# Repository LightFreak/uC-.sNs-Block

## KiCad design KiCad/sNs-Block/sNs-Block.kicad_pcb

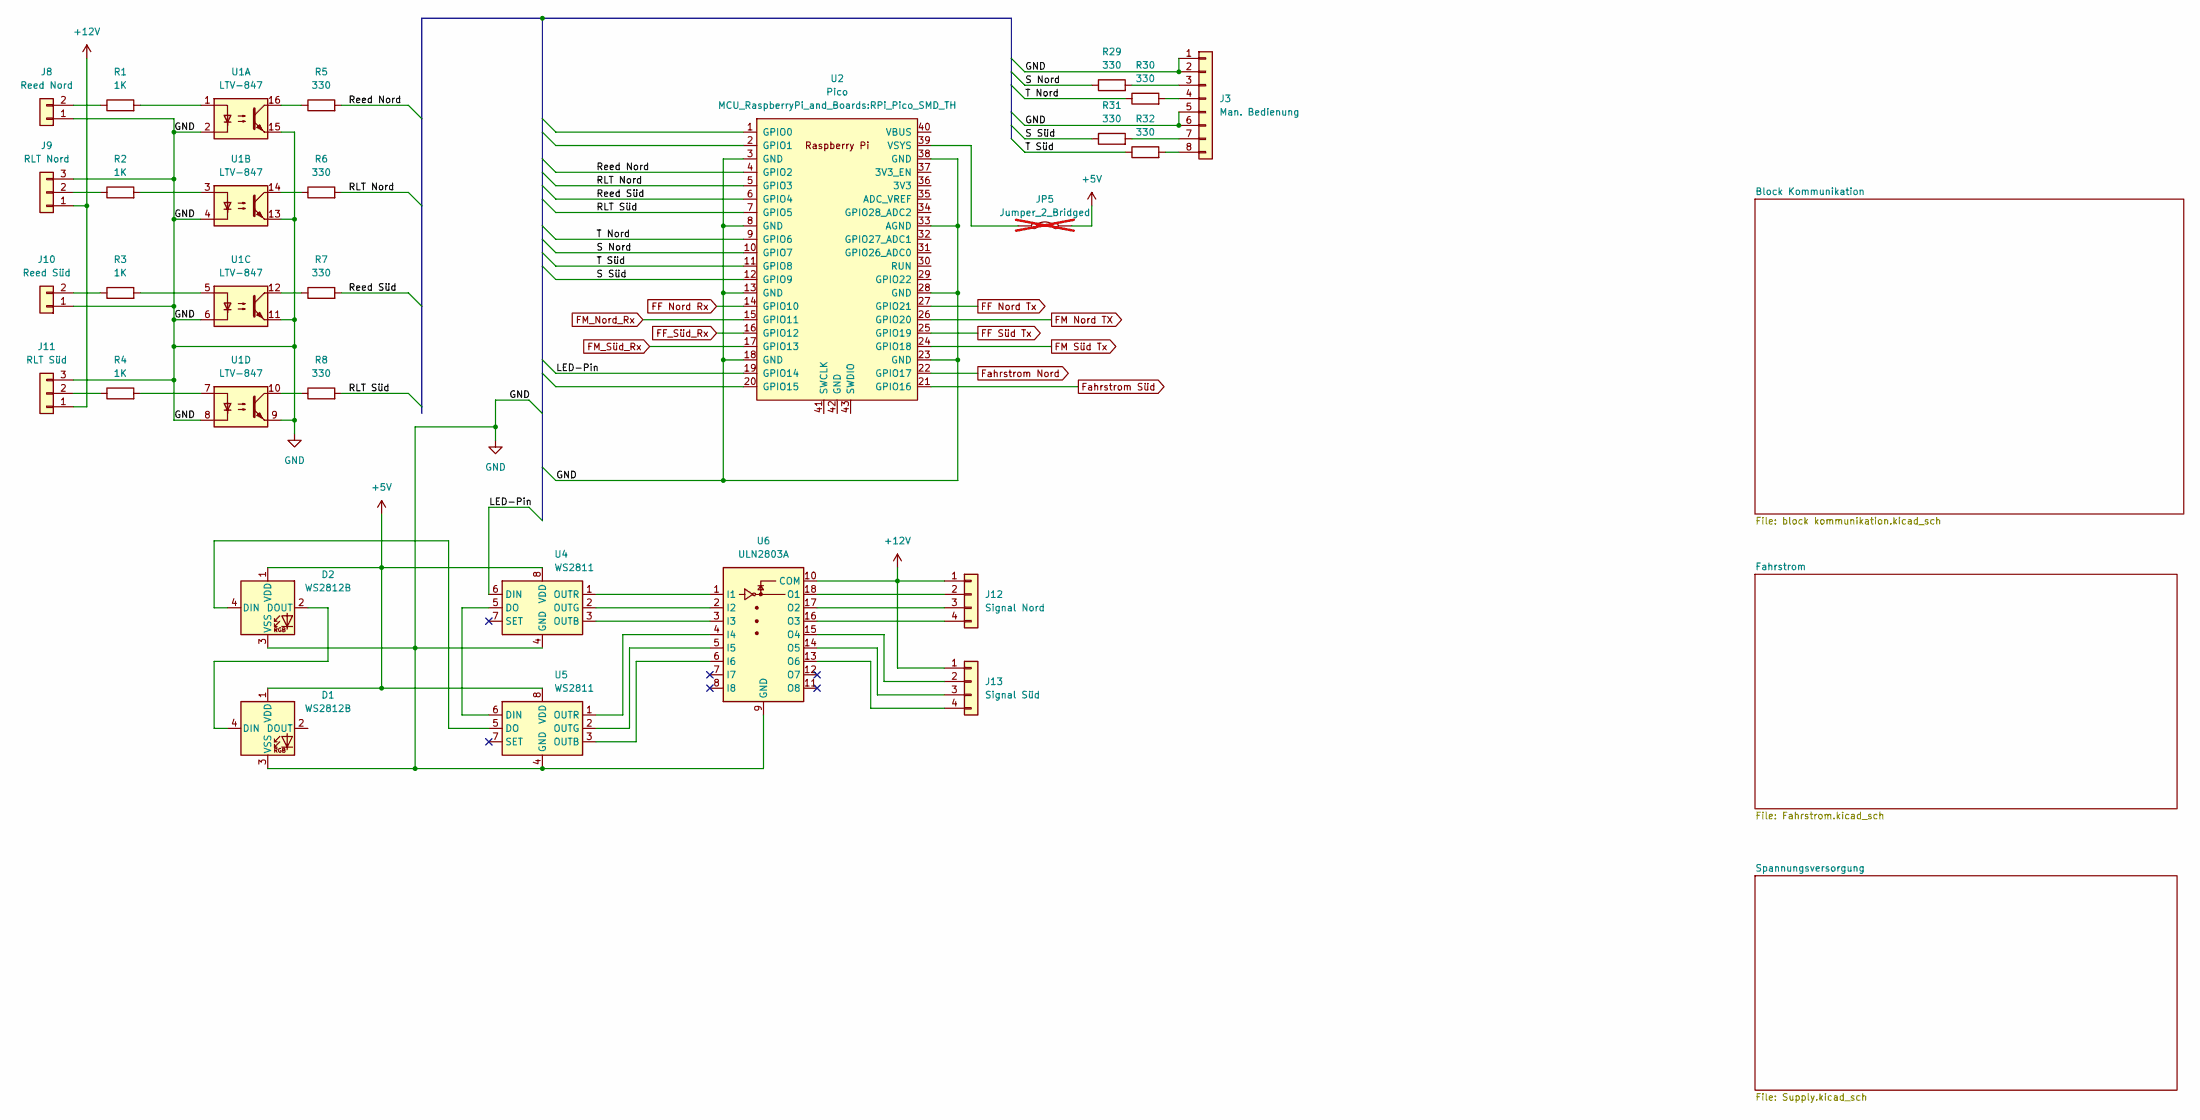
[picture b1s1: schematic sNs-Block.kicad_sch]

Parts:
D1, D2: WS2812B; LED_WS2812B_PLCC4_5.0x5.0mm_P3.2mm; Mouser 474-COM-24837
J3: Man. Bedienung; PinSocket_1x08_P2.54mm_Vertical; Mouser 571-3-641215-8
J8: Reed Nord; PinHeader_1x02_P2.54mm_Vertical; Mouser 571-6445182
J9: RLT Nord; PinHeader_1x03_P2.54mm_Vertical; Mouser 571-6404543
J10: Reed Süd; PinHeader_1x02_P2.54mm_Vertical; Mouser 571-6445182
J11: RLT Süd; PinHeader_1x03_P2.54mm_Vertical; Mouser 571-6404543
J12: Signal Nord; PinHeader_1x04_P2.54mm_Vertical; Mouser 571-6412154
J13: Signal Süd; PinHeader_1x04_P2.54mm_Vertical; Mouser 571-6412154
JP5: Jumper_2_Bridged; TestPoint_2Pads_Pitch5.08mm_Drill1.3mm; not fitted
R1, R2, R3, R4: 1K; R_0805_2012Metric_Pad1.20x1.40mm_HandSolder; Mouser 71-TNPW08051K00FEEA
R5, R6, R7, R8, R29, R30, R31, R32: 330; R_0805_2012Metric_Pad1.20x1.40mm_HandSolder; Mouser 71-CRCW0805330RJNEAH
U1: LTV-847; DIP-16_W7.62mm; Mouser 859-LTV-847
U2: Pico; RPi_Pico_SMD_TH; Mouser 909-RP2040-PICO
U4, U5: WS2811; DIP-8_W7.62mm; Mouser 485-1378
U6: ULN2803A; DIP-18_W7.62mm_Socket; Mouser 511-ULN2803A

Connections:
+5V: D1.1 (VDD), D2.1 (VDD), JP5.2 (B), U4.8 (VDD), U5.8 (VDD); also elsewhere on the board
+12V: J9.1, J11.1, J12.1, J13.1, U6.10 (COM); also elsewhere on the board
/LED-Pin: U2.19 (GPIO14), U4.6 (DIN)
/RLT Nord: R6.2, U2.5 (GPIO3)
/RLT Süd: R8.2, U2.7 (GPIO5)
/Reed Nord: R5.2, U2.4 (GPIO2)
/Reed Süd: R7.2, U2.6 (GPIO4)
/S Nord: R29.1, U2.10 (GPIO7)
/S Süd: R31.1, U2.12 (GPIO9)
/T Nord: R30.1, U2.9 (GPIO6)
/T Süd: R32.1, U2.11 (GPIO8)
FF Nord Rx: U2.14 (GPIO10); also elsewhere on the board
FF Nord Tx: U2.27 (GPIO21); also elsewhere on the board
FF Süd Tx: U2.25 (GPIO19); also elsewhere on the board
FF_Süd_Rx: U2.16 (GPIO12); also elsewhere on the board
FM Nord TX: U2.26 (GPIO20); also elsewhere on the board
FM Süd Tx: U2.24 (GPIO18); also elsewhere on the board
FM_Nord_Rx: U2.15 (GPIO11); also elsewhere on the board
FM_Süd_Rx: U2.17 (GPIO13); also elsewhere on the board
Fahrstrom Nord: U2.22 (GPIO17); also elsewhere on the board
Fahrstrom Süd: U2.21 (GPIO16); also elsewhere on the board
GND: D1.3 (VSS), D2.3 (VSS), J3.1, J3.2, J3.5, J3.6, J8.1, J9.3, J10.1, J11.3, U1.2, U1.4, U1.6, U1.8, U1.9, U1.11, U1.13, U1.15, U2.3 (GND), U2.8 (GND), U2.13 (GND), U2.18 (GND), U2.23 (GND), U2.28 (GND), U2.33 (AGND), U2.38 (GND), U4.4 (GND), U5.4 (GND), U6.9 (GND); also elsewhere on the board
unnamed: D1.4 (DIN), D2.2 (DOUT)
unnamed: D2.4 (DIN), U5.5 (DO)
unnamed: J3.3, R29.2
unnamed: J3.4, R30.2
unnamed: J3.7, R31.2
unnamed: J3.8, R32.2
unnamed: J8.2, R1.1
unnamed: J9.2, R2.1
unnamed: J10.2, R3.1
unnamed: J11.2, R4.1
unnamed: J12.2, U6.18 (O1)
unnamed: J12.3, U6.17 (O2)
unnamed: J12.4, U6.16 (O3)
unnamed: J13.2, U6.15 (O4)
unnamed: J13.3, U6.14 (O5)
unnamed: J13.4, U6.13 (O6)
unnamed: JP5.1 (A), U2.39 (VSYS)
unnamed: R1.2, U1.1
unnamed: R2.2, U1.3
unnamed: R3.2, U1.5
unnamed: R4.2, U1.7
unnamed: R5.1, U1.16
unnamed: R6.1, U1.14
unnamed: R7.1, U1.12
unnamed: R8.1, U1.10
unnamed: U4.5 (DO), U5.6 (DIN)
unnamed: U4.3 (OUTB), U6.3 (I3)
unnamed: U4.2 (OUTG), U6.2 (I2)
unnamed: U4.1 (OUTR), U6.1 (I1)
unnamed: U5.3 (OUTB), U6.6 (I6)
unnamed: U5.2 (OUTG), U6.5 (I5)
unnamed: U5.1 (OUTR), U6.4 (I4)

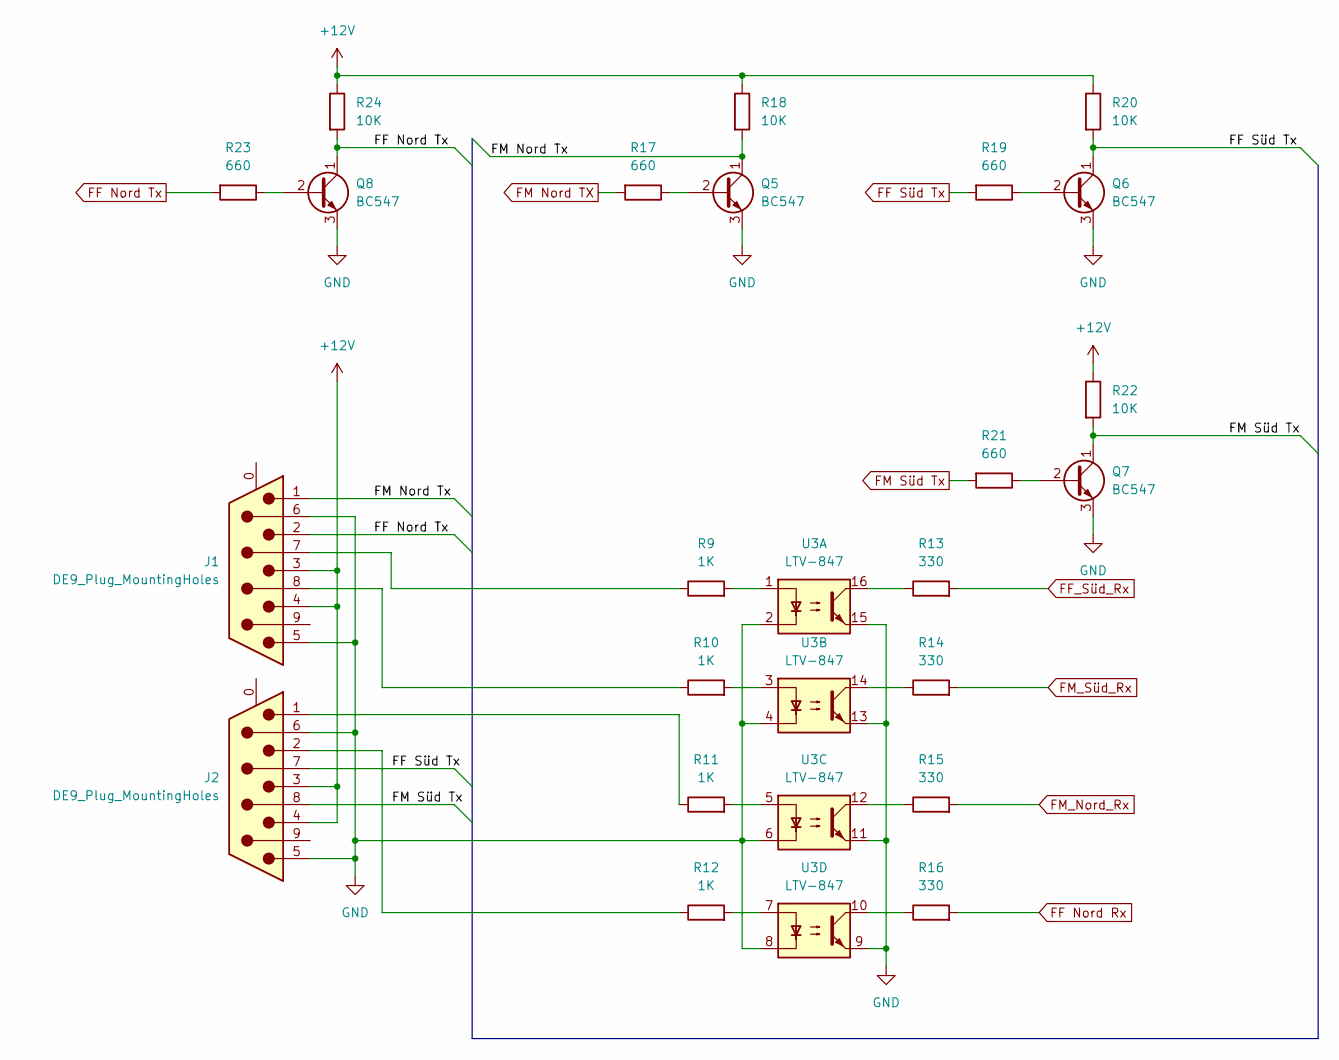
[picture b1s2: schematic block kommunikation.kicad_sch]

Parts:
J1: DE9_Plug_MountingHoles; DSUB-9_Female_Horizontal_P2.77x2.84mm_EdgePinOffset4.94mm_H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; Mouser 523-SDE09SA4CH3FC309
J2: DE9_Plug_MountingHoles; DSUB-9_Male_Horizontal_P2.77x2.84mm_EdgePinOffset4.94mm_Hou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; Mouser 706-163C17529X
Q5, Q6, Q7, Q8: BC547; TO-92_Inline; Mouser 637-BC547C
R9, R10, R11, R12: 1K; R_0805_2012Metric_Pad1.20x1.40mm_HandSolder; Mouser 71-TNPW08051K00FEEA
R13, R14, R15, R16: 330; R_0805_2012Metric_Pad1.20x1.40mm_HandSolder; Mouser 71-CRCW0805330RJNEAH
R17, R19, R21, R23: 660; R_0805_2012Metric_Pad1.20x1.40mm_HandSolder; Mouser 667-ERA-6AEB681V
R18, R20, R22, R24: 10K; R_0805_2012Metric_Pad1.20x1.40mm_HandSolder; Mouser 594-MCU08050D1002BP1
U3: LTV-847; DIP-16_W7.62mm; Mouser 859-LTV-847

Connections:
+12V: J1.3, J1.4, J2.3, J2.4, R18.1, R20.1, R22.1, R24.1; also elsewhere on the board
/Block Kommunikation/FM Nord Tx: J1.1, Q5.1 (C), R18.2
FF Nord Rx: R16.2; also elsewhere on the board
FF Nord Tx: J1.2, Q8.1 (C), R23.2, R24.2; also elsewhere on the board
FF Süd Tx: J2.7, Q6.1 (C), R19.2, R20.2; also elsewhere on the board
FF_Süd_Rx: R13.2; also elsewhere on the board
FM Nord TX: R17.2; also elsewhere on the board
FM Süd Tx: J2.8, Q7.1 (C), R21.2, R22.2; also elsewhere on the board
FM_Nord_Rx: R15.2; also elsewhere on the board
FM_Süd_Rx: R14.2; also elsewhere on the board
GND: J1.5, J1.6, J2.5, J2.6, Q5.3 (E), Q6.3 (E), Q7.3 (E), Q8.3 (E), U3.2, U3.4, U3.6, U3.8, U3.9, U3.11, U3.13, U3.15; also elsewhere on the board
unnamed: J1.7, R9.1
unnamed: J1.8, R10.1
unnamed: J2.1, R11.1
unnamed: J2.2, R12.1
unnamed: Q5.2 (B), R17.1
unnamed: Q6.2 (B), R19.1
unnamed: Q7.2 (B), R21.1
unnamed: Q8.2 (B), R23.1
unnamed: R9.2, U3.1
unnamed: R10.2, U3.3
unnamed: R11.2, U3.5
unnamed: R12.2, U3.7
unnamed: R13.1, U3.16
unnamed: R14.1, U3.14
unnamed: R15.1, U3.12
unnamed: R16.1, U3.10

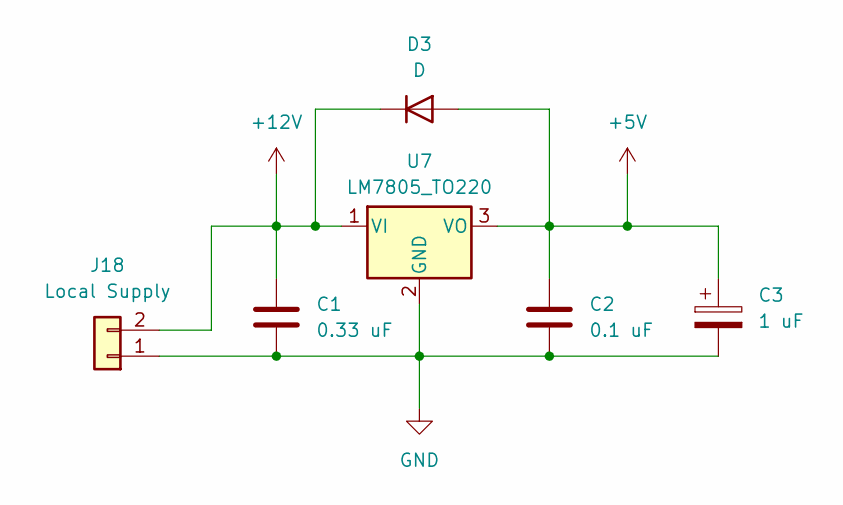
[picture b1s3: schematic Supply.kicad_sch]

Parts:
C1: 0.33 uF; C_0805_2012Metric; Mouser 667-ECH-U1H331JB5
C2: 0.1 uF; C_0805_2012Metric; Mouser 667-ECH-U1H101JX5
C3: 1 uF; CP_Radial_D10.0mm_P5.00mm; Mouser 871-B41821A6227M000
D3: D; D_DO-41_SOD81_P7.62mm_Horizontal; Mouser 637-1N4001
J18: Local Supply; PinSocket_1x02_P2.54mm_Vertical; Mouser 571-6445182
U7: LM7805_TO220; TO-220-3_Vertical; Mouser 926-LM7805CT/NOPB

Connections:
+5V: C2.1, C3.1, D3.2 (A), U7.3 (VO); also elsewhere on the board
+12V: C1.1, D3.1 (K), J18.2, U7.1 (VI); also elsewhere on the board
GND: C1.2, C2.2, C3.2, J18.1, U7.2 (GND); also elsewhere on the board

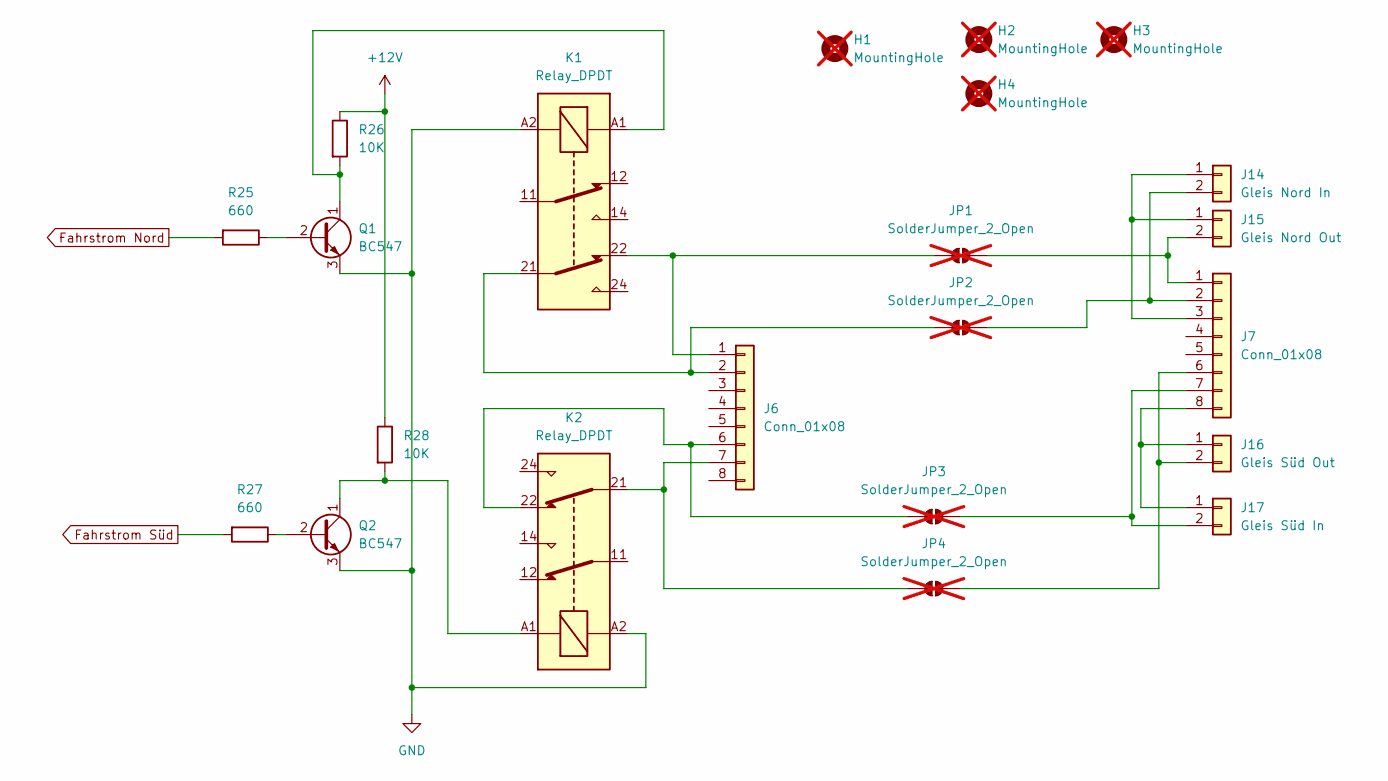
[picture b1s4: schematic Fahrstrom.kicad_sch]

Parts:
H1, H2, H3, H4: MountingHole; MountingHole_4.3mm_M4; not fitted
J6, J7: Conn_01x08; PinSocket_1x08_P2.54mm_Vertical; Mouser 571-3-641215-8
J14: Gleis Nord In; PinSocket_1x02_P2.54mm_Vertical; Mouser 571-6445182
J15: Gleis Nord Out; PinSocket_1x02_P2.54mm_Vertical; Mouser 571-6445182
J16: Gleis Süd Out; PinSocket_1x02_P2.54mm_Vertical; Mouser 571-6445182
J17: Gleis Süd In; PinSocket_1x02_P2.54mm_Vertical; Mouser 571-6445182
JP1, JP2, JP3, JP4: SolderJumper_2_Open; SolderJumper-2_P1.3mm_Open_TrianglePad1.0x1.5mm; not fitted
K1, K2: Relay_DPDT; Relay_DPDT_Finder_30.22; Mouser 653-G6A234PST15USD12
Q1, Q2: BC547; TO-92_Inline; Mouser 637-BC547C
R25, R27: 660; R_0805_2012Metric_Pad1.20x1.40mm_HandSolder; Mouser 667-ERA-6AEB681V
R26, R28: 10K; R_0805_2012Metric_Pad1.20x1.40mm_HandSolder; Mouser 594-MCU08050D1002BP1

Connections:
+12V: R26.1, R28.1; also elsewhere on the board
Fahrstrom Nord: R25.2; also elsewhere on the board
Fahrstrom Süd: R27.2; also elsewhere on the board
GND: K1.A2, K2.A2, Q1.3 (E), Q2.3 (E); also elsewhere on the board
unnamed: J6.1, JP1.1 (A), K1.22
unnamed: J6.2, JP2.1 (A), K1.21
unnamed: J6.6, JP3.1 (A), K2.22
unnamed: J6.7, JP4.1 (A), K2.21
unnamed: J7.3, J14.1, J15.1
unnamed: J7.2, J14.2, JP2.2 (B)
unnamed: J7.1, J15.2, JP1.2 (B)
unnamed: J7.8, J16.1, J17.1
unnamed: J7.6, J16.2, JP4.2 (B)
unnamed: J7.7, J17.2, JP3.2 (B)
unnamed: Q1.2 (B), R25.1
unnamed: K1.A1, Q1.1 (C), R26.2
unnamed: Q2.2 (B), R27.1
unnamed: K2.A1, Q2.1 (C), R28.2

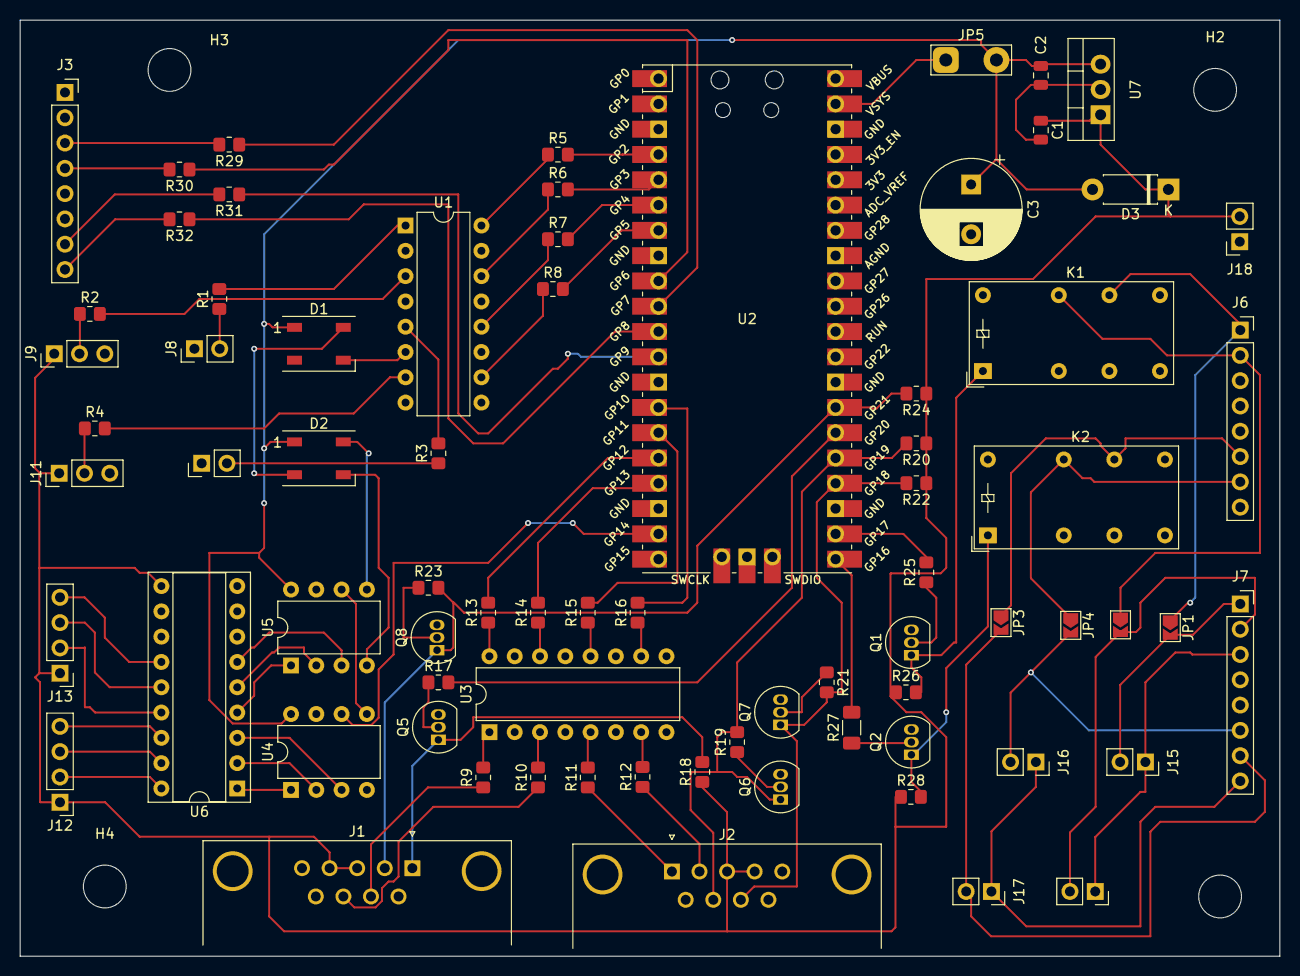
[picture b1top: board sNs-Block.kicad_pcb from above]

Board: 2 copper layers, 126.5 x 94.0 mm, 78 parts (0 on the bottom side), 85 nets.

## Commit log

2024-05-01 Init Local
2024-05-04 Add Fastled for Signaling
2024-05-08 Layout & Schema
